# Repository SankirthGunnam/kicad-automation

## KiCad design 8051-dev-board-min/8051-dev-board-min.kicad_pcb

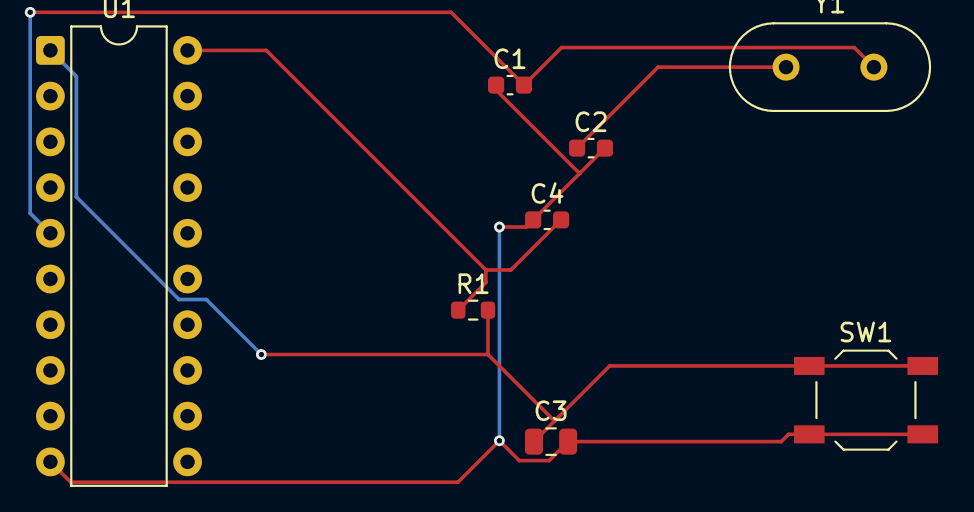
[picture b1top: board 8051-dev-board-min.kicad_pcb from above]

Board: 2 copper layers, 8 parts (0 on the bottom side), 5 nets.

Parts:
C1, C2: 22pF; C_0603_1608Metric
C3: 10uF; C_0805_2012Metric
C4: 100nF; C_0603_1608Metric
R1: 10k; R_0603_1608Metric
SW1: RESET; SW_SPST_TL3342
U1: AT89S4051-24P; DIP-20_W7.62mm
Y1: 11.0592MHz; Crystal_HC49-U_Vertical

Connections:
+5V: C4.2, R1.1, U1.20 (VCC)
/RST: C3.1, R1.2, SW1.1, U1.1 (RST/VPP)
/XTAL1: C1.2, U1.5 (XTAL1), Y1.2
GND: C1.1, C2.2, C3.2, C4.1, SW1.2, U1.10 (GND)
unnamed: C2.1, Y1.1
